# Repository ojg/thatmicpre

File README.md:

ThatMicPre
=====
A simple, high-quality DIY microphone pre-amplifier with switched gain.

The background for this project was that I needed a simple but good microphone preamp for doing acoustic measurements. I needed a switched gain to be able to reproduce the gain setting in a more predictable way than what is possible with a potmeter. I could not find any existing DIY designs, so I decided to make one.

The design is based on the excellent [THAT1510 or THAT1512](https://thatcorp.com/that-1510-1512-low-noise-high-performance-audio-preamplifiers/) preamp ICs. It is also compatible with [SSM2019](https://www.analog.com/en/products/ssm2019.html) or [INA217](https://www.ti.com/product/INA217). I have followed all THAT's datasheets and app-notes to implement a robust, best-practice design.

A goal was to use simple through-hole parts that I and other DIYers usually have in our parts drawer. So there are no additional IC's or voltage regulators for example, it just uses simple transistors, capacitors and zener diodes for supply filtering and regulation. I selected affordable switches and connectors to keep cost down. Many parts can be substituted without sacrificing performance.

There are two versions of this design, one suited for a desktop encolsure with gain switch on top, and one suited for a rack-mount enclosure with gain switch on the front.

There is a separate PCB project in the panels folder that contains PCB layout for front and back panels that fits the 1455K120x case. Since it is copper-clad on the inside, it makes for a nice shielded box.

This is an open-source project released under CC-BY-SA-4.0 license. It basically means you can use it as you want as long as you share modifications under the same license, and attribute back to this project. See [LICENSE.txt](../blob/master/LICENSE.txt) for details.

See discussion of this project in this [DIYAudio thread.](https://www.diyaudio.com/forums/equipment-and-tools/356317-thatmicpre-source-mic-preamp.html) If you decide to build this pre-amplifier, please post results of your build there.

Specifications
-----
* Microphone preamplifier with switched gain and 48V phantom power.
* XLR input and output connectors.
* Phantom power on/off switch.
* Phase invert switch.
* Gains (dB): 0, 10, 15, 20, 25, 30, 35, 40, 45, 50, 55, 60.
* Gain deviation from nominal: Max +/-0.5dB using R12-series resistors.
* Frequency response: 0/-3dB from 10Hz to 100kHz for all gain settings.
* Input impedance: 2.0kohm differential (1kHz)
* Impedance balanced output, output impedance 200ohm (1kHz)
* Max output level: 20dBu at 0.1% THD (1kHz).
* THD+N less than 0.005% at 1kHz at 18dBu output level for all gain settings (20-20kHz BW).
* 48V DC power supply required, 30mA max. 
  * (Will operate with lower voltage DC power supplies with reduced phantom voltage and max output level).
* PCB dimensions 75mm x 120mm, fits the [Hammond 1455K120x](https://www.hammfg.com/part/1455K1201) enclosure.
  * Desktop version has gain switch on top of enclosure for easy access.
  * Rack version has gain switch on front for easy mounting in a rack enclosure.

Photos
-----
#### Desktop version

(PCBA credit jsenderatx on diyaudio)

#### Rack version

The rack version has a PCB where one part separates. This part contains the gain resistors and switch.
It mounts at a right angle to the main PCB with two angled female headers underneath main PCB. See BOM.

## Bill of Materials
Nicely formatted BOM is in the plots folder for [desktop version](https://htmlpreview.github.io/?https://github.com/ojg/thatmicpre/blob/master/desktop/plots/thatmicpre_bom.html)
and [rack version](https://htmlpreview.github.io/?https://github.com/ojg/thatmicpre/blob/master/rack/plots/thatmicpre_v2_bom.html).

Thanks to the [InteractiveHtmlBom project](https://github.com/openscopeproject/InteractiveHtmlBom).

Schematic
-----
#### Desktop version

#### Rack version

Measurements
-----
### Output noise vs gain
20-22kHz BW un-wtd, 150ohm source impedance.
Note: Theoretical minimum EIN with 150ohm source impedance is -130.4dBu.

| Gain(dB) | THAT1510<br />Output Noise (dBu) | THAT1510<br />EIN (dBu) | THAT1512<br />Output Noise (dBu) | THAT1512<br />EIN (dBu) |
| --- | --- | --- |--- | --- |
| 0 | -98.5 | -98.5 | -102.4 | -102.4 |
| 10 | -98.2 | -108.2 | -102.0 | -112.0 |
| 15 | -97.8 | -112.8 | -101.3 | -116.3 |
| 20 | -96.8 | -116.8 | -100.0 | -120.0 |
| 25 | -95.6 | -120.6 | -98.0 | -123.0 |
| 30 | -93.2 | -123.2 | -95.2 | -125.2 |
| 35 | -89.8 | -124.8 | -91.5 | -126.5 |
| 40 | -86.8 | -126.8 | -87.3 | -127.3 |
| 45 | -82.6 | -127.6 | -82.8 | -127.8 |
| 50 | -77.8 | -127.8 | -78.1 | -128.1 |
| 55 | -73.1 | -128.1 | -73.3 | -128.3 |
| 60 | -68.3 | -128.3 | -68.6 | -128.6 |

### Frequency Response
#### THAT1510 with 1% R12 resistors

#### THAT1512 with 1% R96 resistors

### THD+N vs Frequency
#### THAT1510

#### THAT1512

### THD+N vs Amplitude
#### THAT1510

#### THAT1512

### Common Mode Rejection Ratio
#### THAT1510

#### THAT1512

### Bandpass Noise Level
Note no measureable hum.
#### THAT1510

#### THAT1512

---
OJG 2023

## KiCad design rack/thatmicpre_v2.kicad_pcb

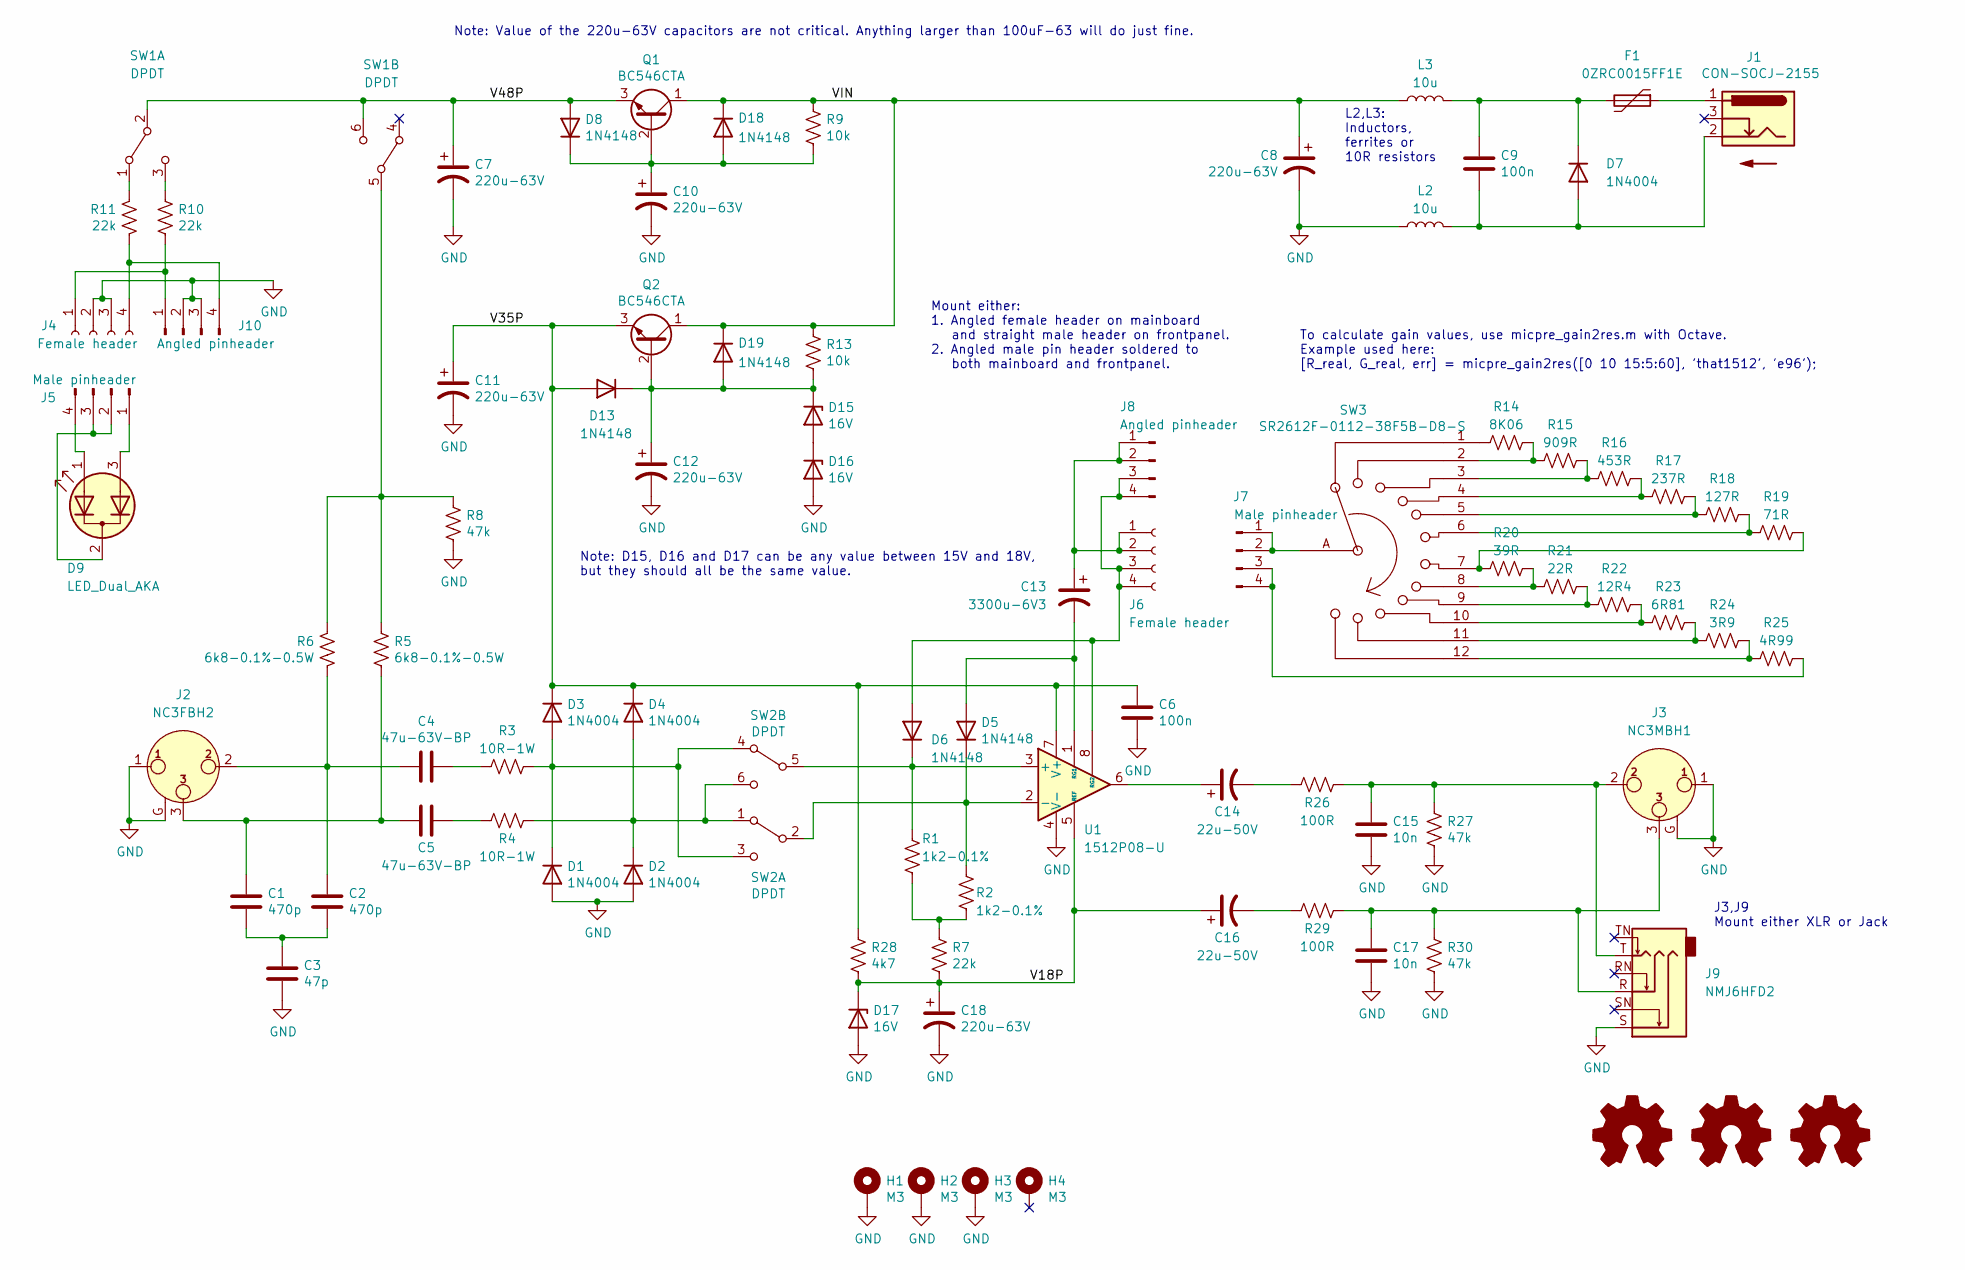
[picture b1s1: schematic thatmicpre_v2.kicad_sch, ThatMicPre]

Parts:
C1, C2: 470p; C_Disc_D5.0mm_W2.5mm_P5.00mm; Mfr Part Nr FG28C0G2A471JNT0
C3: 47p; C_Disc_D5.0mm_W2.5mm_P5.00mm; Mfr Part Nr FG28C0G2A470JNT0
C4, C5: 47u-63V-BP; C_Radial_D10.0mm_H16.0mm_P5.00mm; Mfr Part Nr UVP1J470MPD
C6, C9: 100n; C_Rect_L7.2mm_W3.0mm_P5.00mm_FKS2_FKP2_MKS2_MKP2; Mfr Part Nr R82EC3100AA70J
C7, C8, C10, C11, C12, C18: 220u-63V; CP_Radial_D10.0mm_P5.00mm; Mfr Part Nr UPW1J221MPD
C13: 3300u-6V3; CP_Radial_D10.0mm_P5.00mm; Mfr Part Nr UFW0J332MPD
C14, C16: 22u-50V; CP_Radial_D6.3mm_P2.50mm; Mfr Part Nr UEP1V220MED
C15, C17: 10n; C_Rect_L7.2mm_W3.0mm_P5.00mm_FKS2_FKP2_MKS2_MKP2; Mfr Part Nr PHE426DJ5100JR05
D1, D2, D3, D4, D7: 1N4004; D_DO-41_SOD81_P10.16mm_Horizontal; Mfr Part Nr 1N4004GP
D5, D6, D8, D13, D18, D19: 1N4148; D_DO-34_SOD68_P7.62mm_Horizontal; Mfr Part Nr 1N4148
D9: LED_Dual_AKA; LED_D5.0mm-3; Mfr Part Nr WP59EGW
D15, D16, D17: 16V; D_DO-34_SOD68_P7.62mm_Horizontal; Mfr Part Nr BZX55B16
F1: 0ZRC0015FF1E; Fuse_BelFuse_0ZRE0005FF_L8.3mm_W3.8mm; Mfr Part Nr 0ZRC0015FF1E
H1, H2, H3, H4: M3; MountingHole_3.2mm_M3_Pad
J1: CON-SOCJ-2155; BarrelJack_Horizontal; Mfr Part Nr CON-SOCJ-2155
J2: NC3FBH2; Jack_XLR_Neutrik_NC3FBH2_Horizontal; Mfr Part Nr NC3FBH2
J3: NC3MBH1; Jack_XLR_Neutrik_NC3MBH_Horizontal; Mfr Part Nr NC3MBH1
J4, J6: Female header; PinSocket_1x04_P2.54mm_Horizontal; Mfr Part Nr SSQ-104-02-T-S-RA
J5, J7: Male pinheader; PinHeader_1x04_P2.54mm_Vertical; Mfr Part Nr TSW-104-07-T-S
J8, J10: Angled pinheader; PinHeader_1x04_P2.54mm_Vertical; Mfr Part Nr TSW-104-08-F-S-RA
J9: NMJ6HFD2; Jack_6.35mm_Neutrik_NMJ6HFD2_Horizontal; Mfr Part Nr NMJ6HFD2
L2, L3: 10u; L_Axial_L5.3mm_D2.2mm_P10.16mm_Horizontal_Vishay_IM-1; Mfr Part Nr 78F100J-TR-RC
LOGO1: Logo_Open_Hardware_Small; OSHW-Symbol_6.7x6mm_Copper
LOGO2: Logo_Open_Hardware_Small; Symbol_CC-Attribution_CopperTop_Small
LOGO3: Logo_Open_Hardware_Small; Symbol_CreativeCommons_CopperTop_Type2_Small
LOGO4: SYM_Arrow_Normal; Symbol_Barrel_Polarity
Q1, Q2: BC546CTA; TO-92_Inline_Wide; Mfr Part Nr BC546CTA
R1, R2: 1k2-0.1%; R_Axial_DIN0207_L6.3mm_D2.5mm_P10.16mm_Horizontal; Mfr Part Nr YR1B1K21CC
R3, R4: 10R-1W; R_Axial_DIN0207_L6.3mm_D2.5mm_P10.16mm_Horizontal; Mfr Part Nr CPF110R000FEB14
R5, R6: 6k8-0.1%-0.5W; R_Axial_DIN0207_L6.3mm_D2.5mm_P10.16mm_Horizontal; Mfr Part Nr CMF556K8100BEEK
R7, R10, R11: 22k; R_Axial_DIN0207_L6.3mm_D2.5mm_P10.16mm_Horizontal; Mfr Part Nr MBB02070C2202FCT00
R8, R27, R30: 47k; R_Axial_DIN0207_L6.3mm_D2.5mm_P10.16mm_Horizontal; Mfr Part Nr MBB02070C4702FCT00
R9, R13: 10k; R_Axial_DIN0207_L6.3mm_D2.5mm_P10.16mm_Horizontal; Mfr Part Nr MBB02070C1002FCT00
R14: 8K06; R_Axial_DIN0207_L6.3mm_D2.5mm_P10.16mm_Horizontal; Mfr Part Nr MFR50SFTE52-8K06
R15: 909R; R_Axial_DIN0207_L6.3mm_D2.5mm_P10.16mm_Horizontal; Mfr Part Nr MFR50SFTE52-909R
R16: 453R; R_Axial_DIN0207_L6.3mm_D2.5mm_P10.16mm_Horizontal; Mfr Part Nr MFR50SFTE52-453R
R17: 237R; R_Axial_DIN0207_L6.3mm_D2.5mm_P10.16mm_Horizontal; Mfr Part Nr MFR50SFTE52-237R
R18: 127R; R_Axial_DIN0207_L6.3mm_D2.5mm_P10.16mm_Horizontal; Mfr Part Nr MFR50SFTE52-127R
R19: 71R; R_Axial_DIN0207_L6.3mm_D2.5mm_P10.16mm_Horizontal; Mfr Part Nr MFR50SFTE52-71R
R20: 39R; R_Axial_DIN0207_L6.3mm_D2.5mm_P10.16mm_Horizontal; Mfr Part Nr MFR50SFTE52-39R
R21: 22R; R_Axial_DIN0207_L6.3mm_D2.5mm_P10.16mm_Horizontal; Mfr Part Nr MFR50SFTE52-22R
R22: 12R4; R_Axial_DIN0207_L6.3mm_D2.5mm_P10.16mm_Horizontal; Mfr Part Nr MFR50SFTE52-12R4
R23: 6R81; R_Axial_DIN0207_L6.3mm_D2.5mm_P10.16mm_Horizontal; Mfr Part Nr MFR50SFTE52-6R81
R24: 3R9; R_Axial_DIN0207_L6.3mm_D2.5mm_P10.16mm_Horizontal; Mfr Part Nr MFR50SFTE52-3R9
R25: 4R99; R_Axial_DIN0207_L6.3mm_D2.5mm_P10.16mm_Horizontal; Mfr Part Nr MFR50SFTE52-4R99
R26, R29: 100R; R_Axial_DIN0207_L6.3mm_D2.5mm_P10.16mm_Horizontal; Mfr Part Nr MFR50SFTE52-100R
R28: 4k7; R_Axial_DIN0207_L6.3mm_D2.5mm_P10.16mm_Horizontal; Mfr Part Nr MBB02070C4701FCT00
SW1, SW2: DPDT; SW_PBH2UEESNPNAGX; Mfr Part Nr PBH2UEESNPNAGX
SW3: SR2612F-0112-38F5B-D8-S; LORINCK1049; Mfr Part Nr SR2612F-0112
U1: 1512P08-U; DIP-8_W7.62mm; Mfr Part Nr 1512P08-U

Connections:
/V18P: C16.1, C18.1, D17.1 (K), R7.2, R28.2, U1.5 (REF)
/V35P: C6.1, C11.1, D3.1 (K), D4.1 (K), D13.2 (A), Q2.3 (E), R28.1, U1.7 (V+)
/V48P: C7.1, D8.2 (A), Q1.3 (E), SW1.2 (B), SW1.6 (C)
/VIN: C8.1, D18.1 (K), D19.1 (K), L3.1, Q1.1 (C), Q2.1 (C), R9.1, R13.1
GND: C3.2, C6.2, C7.2, C8.2, C10.2, C11.2, C12.2, C15.2, C17.2, C18.2, D1.2 (A), D2.2 (A), D16.2 (A), D17.2 (A), H1.1, H2.1, H3.1, J2.1, J2.G, J3.1, J3.G, J4.2, J4.3, J9.S, J10.2, J10.3, L2.1, R8.2, R27.2, R30.2, U1.4 (V-)
unnamed: C1.1, C5.1, J2.3, R5.2
unnamed: C1.2, C2.2, C3.1
unnamed: C2.1, C4.1, J2.2, R6.2
unnamed: C4.2, R3.2
unnamed: C5.2, R4.2
unnamed: C9.1, D7.1 (K), F1.2, L3.2
unnamed: C9.2, D7.2 (A), J1.2, L2.2
unnamed: C10.1, D8.1 (K), D18.2 (A), Q1.2 (B), R9.2
unnamed: C12.1, D13.1 (K), D15.1 (K), D19.2 (A), Q2.2 (B), R13.2
unnamed: C13.1, J6.1, J6.2, J8.1, J8.2
unnamed: C13.2, D5.2 (A), U1.1 (RG1)
unnamed: C14.1, U1.6
unnamed: C14.2, R26.2
unnamed: C15.1, J3.2, J9.T, R26.1, R27.1
unnamed: C16.2, R29.2
unnamed: C17.1, J3.3, J9.R, R29.1, R30.1
unnamed: D1.1 (K), D3.2 (A), R3.1, SW2.3 (C), SW2.4 (A)
unnamed: D2.1 (K), D4.2 (A), R4.1, SW2.1 (A), SW2.6 (C)
unnamed: D5.1 (K), R2.1, SW2.2 (B), U1.2 (-)
unnamed: D6.1 (K), R1.1, SW2.5 (B), U1.3 (+)
unnamed: D6.2 (A), J6.3, J6.4, J8.3, J8.4, U1.8 (RG2)
unnamed: D9.1 (A1), J5.4
unnamed: D9.2 (K), J5.2, J5.3
unnamed: D9.3 (A2), J5.1
unnamed: D15.2 (A), D16.1 (K)
unnamed: F1.1, J1.1
unnamed: J7.1, J7.2, SW3.A
unnamed: J7.3, J7.4, R25.2
unnamed: J4.1, J10.1, R10.2
unnamed: J4.4, J10.4, R11.2
unnamed: R1.2, R2.2, R7.1
unnamed: R5.1, R6.1, R8.1, SW1.5 (B)
unnamed: R10.1, SW1.3 (C)
unnamed: R11.1, SW1.1 (A)
unnamed: R14.1, R15.2, SW3.2
unnamed: R14.2, SW3.1
unnamed: R15.1, R16.2, SW3.3
unnamed: R16.1, R17.2, SW3.4
unnamed: R17.1, R18.2, SW3.5
unnamed: R18.1, R19.2, SW3.6
unnamed: R19.1, R20.2, SW3.7
unnamed: R20.1, R21.2, SW3.8
unnamed: R21.1, R22.2, SW3.9
unnamed: R22.1, R23.2, SW3.10
unnamed: R23.1, R24.2, SW3.11
unnamed: R24.1, R25.1, SW3.12

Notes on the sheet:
To calculate gain values, use micpre_gain2res.m with Octave. Example used here: [R_real, G_real, err] = micpre_gain2res([0 10 15:5:60], 'that1512', 'e96');
J3,J9 Mount either XLR or Jack
Mount either: 1. Angled female header on mainboard and straight male header on frontpanel. 2. Angled male pin header soldered to both mainboard and frontpanel.
L2,L3: Inductors, ferrites or 10R resistors
Note: Value of the 220u-63V capacitors are not critical. Anything larger than 100uF-63 will do just fine.
Note: D15, D16 and D17 can be any value between 15V and 18V, but they should all be the same value.

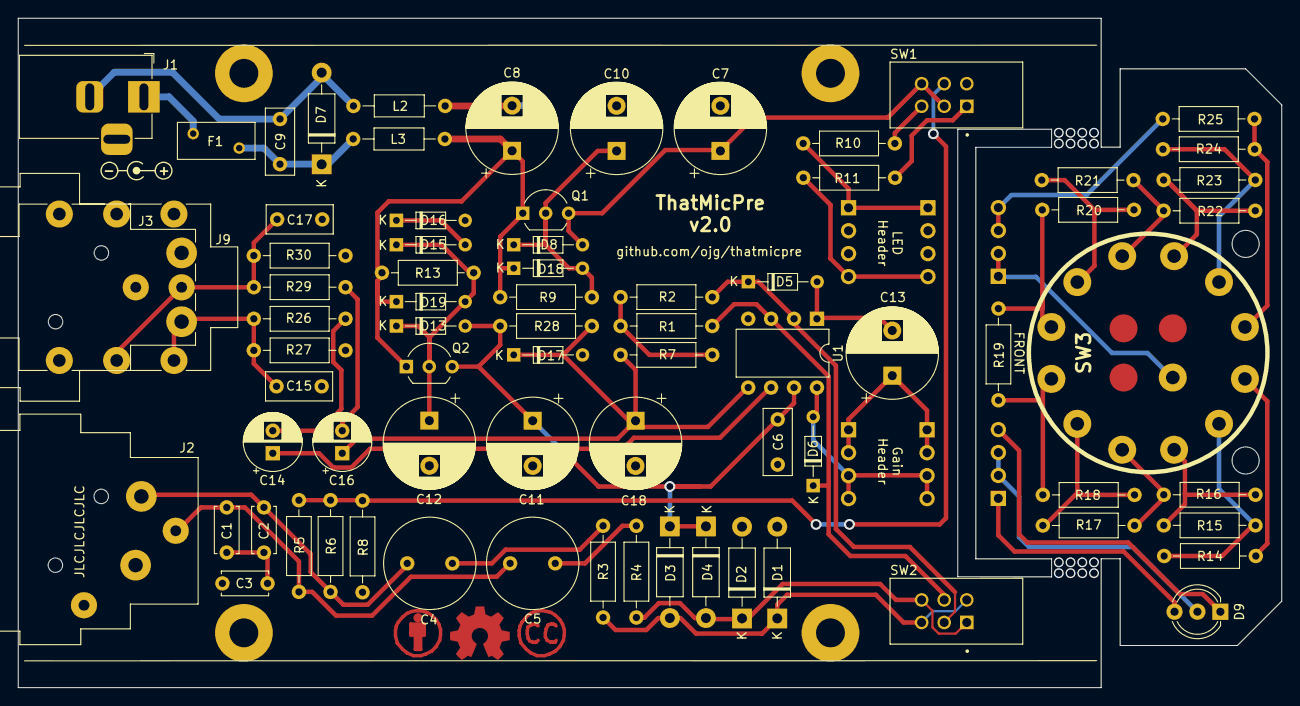
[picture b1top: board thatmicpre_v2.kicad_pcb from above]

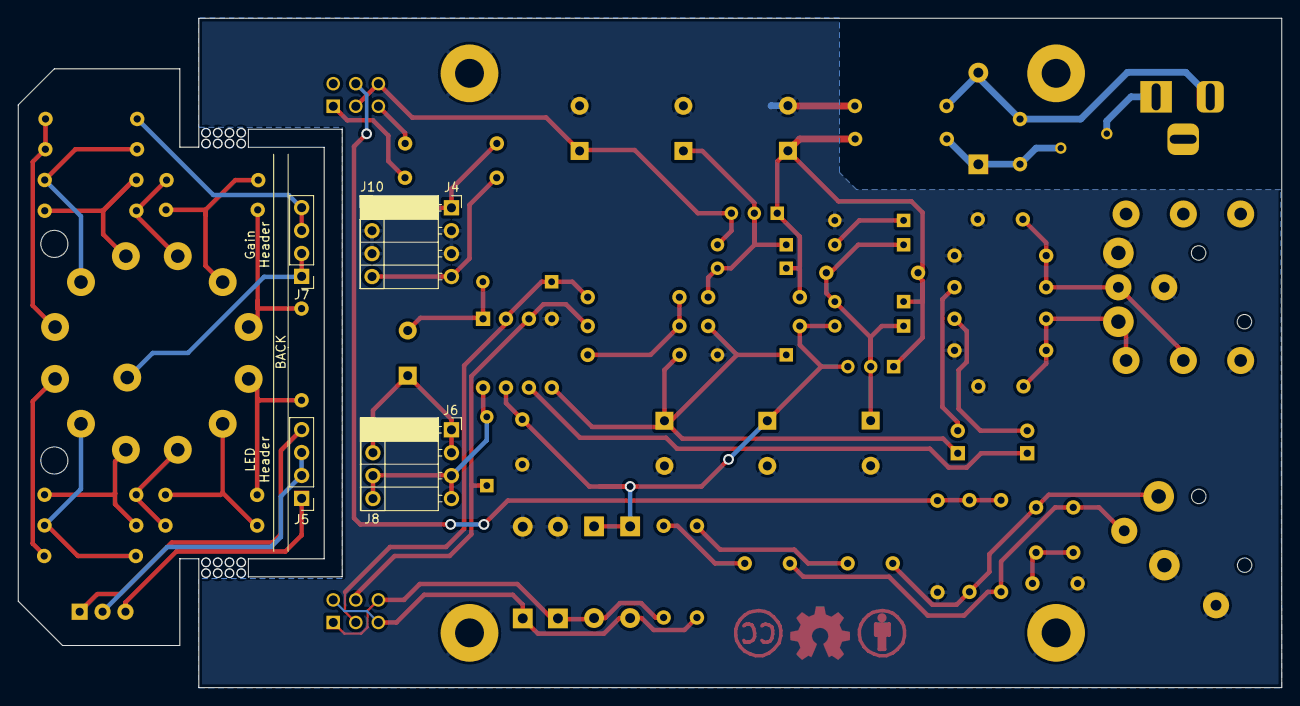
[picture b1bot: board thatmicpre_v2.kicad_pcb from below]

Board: 2 copper layers, 140.0 x 74.2 mm, 89 parts (6 on the bottom side), 51 nets.

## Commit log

2020-05-13 Add sch and pcb v1.0
2020-05-16 Add missing rescue.dcm
2020-06-07 Update readme with project background and goals
2020-06-07 Update to v1.1.
    Add gerbers and pdfs to plots.
2020-06-07 Adding schematic pdf to readme
2020-06-07 Add schemtic pdf to readme take 2
2020-06-07 Add schematic link to readme
2020-06-07 add schematic png
2020-06-07 Add PCB view to readme
2020-06-07 Add docs folder
2020-06-07 Add pcb photo to readme
2020-06-07 Add spec and measurements
2020-06-08 Add .m file to calculate gain resistors. Add comment to schematic
2020-06-08 Add BOM to plots folder
2020-06-09 Resize pictures, remove sch pdf
2021-02-14 Add top panel label drawing
2021-06-07 Added missing drill files to gerbers
2021-06-07 Added link to diyaudio thread
2022-08-02 Update README.md
    Added html links for IC parts
2022-08-21 Update project files to Kicad 6
2022-08-21 Update 3D models
2022-09-01 Updated picture of PCB
2022-10-10 Update XLR cutout radius and silkscreen placement after testfitting
2022-10-10 Add pcb and gerbers for front and backpanels for v1.1
2022-10-10 Replace csv bom with InteractiveHtmlBom
    Update mfr part nr for some resistors and capacitors,
    to more affordable and easily obtained parts.
2022-10-10 Update readme with panels and html-bom
2022-10-10 Add htmlpreview link to html bom
2022-10-10 Fix html bom link
2022-12-17 Correct preamplifier product page hyperlink URL
2023-03-19 Copied v1 design files to rack
2023-03-19 First complete layout of v2
2023-03-19 Move v1.1 files to v1 folder
2023-03-19 Move v1 based plots, docs and pictures to desktop folder
    move panels to desktop
2023-03-19 Production version of v2.0 (rack version) with panels
2023-03-19 Remove PSU option
2023-03-19 optimized layout
    added alternative jack and headers
    checked against prints for mech fit
2023-03-19 Modified rack version BOM to match assembled prototype
2023-03-19 Redo power section layout, add PSU option
2023-03-19 Update readme with 1512 measurements, and v2 schematic
2023-03-19 Update readme with pics of rack version
2023-03-19 Fix bom link
2023-10-01 Rack: Correct gain resistor part numbers
2024-11-06 Update front-panel pcb to use outline instead of solid circle for holes
    Based on feedback that JLCPCB does not handle solids on edge-cut layer well.
